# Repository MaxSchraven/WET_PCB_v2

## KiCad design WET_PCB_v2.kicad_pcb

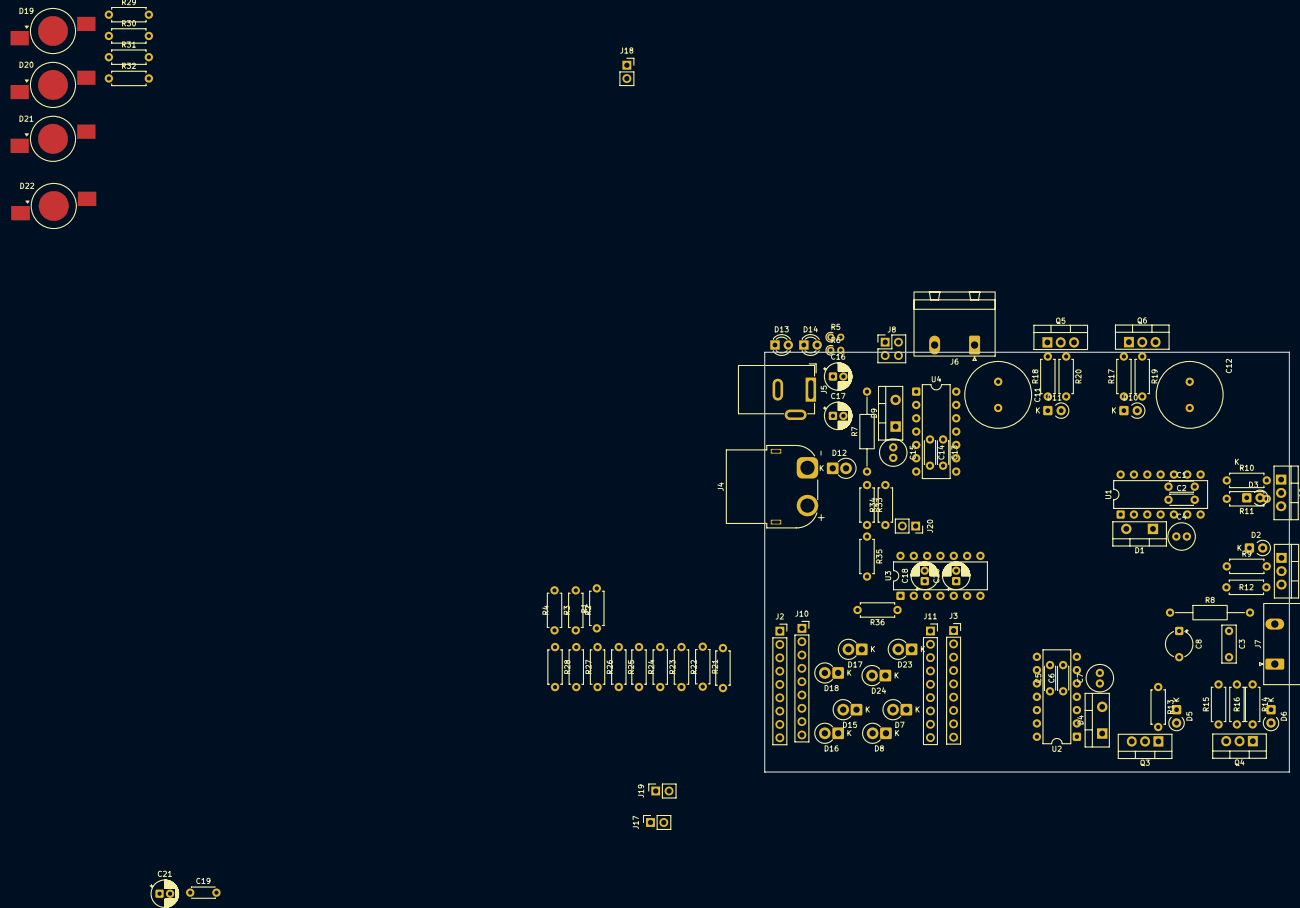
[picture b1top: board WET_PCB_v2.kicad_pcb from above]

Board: 2 copper layers, 100.0 x 80.0 mm, 102 parts (0 on the bottom side), 61 nets, no tracks yet.

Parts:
C1, C2, C5, C6, C13, C14, C19: C322C104K5R5TA; C_Disc_D4.3mm_W1.9mm_P5.00mm
C3: B32529C1104K000; C_Rect_L7.0mm_W2.5mm_P5.00mm
C4, C7, C15: MCGPR63V106M5X11; C_Radial_D5.0mm_H11.0mm_P2.00mm
C8: C; CP_Radial_Tantal_D5.0mm_P5.00mm
C11, C12: C_Polarized; C_Radial_D12.5mm_H20.0mm_P5.00mm
C16, C17, C18, C20, C21: C_Polarized; CP_Radial_D5.0mm_P2.00mm
D1, D4, D9: STPS8H100D; TO-220-2_Vertical
D2, D3, D5, D6, D10, D11: 1N4004; D_A-405_P2.54mm_Vertical_CathodeUp
D7, D8, D15, D16, D17, D18, D23, D24: 1N4004; D_DO-15_P2.54mm_Vertical_CathodeUp
D12: MBR1020VL; D_DO-15_P2.54mm_Vertical_CathodeUp
D13, D14: LED; LED_D3.0mm
D19, D20, D21, D22: LED; LED_1W_3W_R8
J2, J3, J10, J11: Conn_01x09_Pin; PinSocket_1x09_P2.54mm_Vertical
J4: XT60; AMASS_XT60PW-F_1x02_P7.20mm_Horizontal
J5: Barrel jack; BarrelJack_GCT_DCJ200-10-A_Horizontal
J6, J7: Pluggable Terminal Block; PhoenixContact_GMSTBA_2,5_2-G-7,62_1x02_P7.62mm_Horizontal
J8: Jumper; PinHeader_2x02_P2.54mm_Vertical
J17, J18, J19, J20: Capacitor connector; PinSocket_1x02_P2.54mm_Vertical
Q1, Q2, Q3, Q4: IRF530NPBF; TO-220-3_Vertical
Q5, Q6: Q_NMOS_GDS; TO-220-3_Vertical
R1, R2, R3, R4, R21, R22, R23, R24, R25, R26, R27, R28, R29, R30, R31, R32, R33, R34, R35, R36: R; R_Axial_DIN0207_L6.3mm_D2.5mm_P7.62mm_Horizontal
R5, R6: R; R_Axial_DIN0204_L3.6mm_D1.6mm_P1.90mm_Vertical
R7, R8: Shunt; R_Axial_DIN0207_L6.3mm_D2.5mm_P15.24mm_Horizontal
R9, R10, R11, R12, R13, R14, R15, R16, R17, R18, R19, R20: MF25_10K; R_Axial_DIN0207_L6.3mm_D2.5mm_P7.62mm_Horizontal
U1, U2, U4: IR2110; DIP-14_W7.62mm
U3: Opamp_Quad; DIP-14_W7.62mm

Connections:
+5V: C18.1, C19.1, C20.1, C21.1, D7.1 (K), D15.1 (K), D17.1 (K), D23.1 (K), J8.4, R6.1, U3.4 (V+)
+12V: C16.1, C17.1, D1.2 (A), D4.2 (A), J2.9, J5.1, J10.9, R5.1, U1.3 (VCC), U2.3 (VCC)
/ADC1_IN0: J3.5, J11.5
/ADC1_IN1: D15.2 (A), D16.1 (K), D17.2 (A), D18.1 (K), J3.6, J11.6, R22.2, R28.2, U3.8 (out3), U3.14 (out4)
/ADC1_IN4: D7.2 (A), D8.1 (K), J2.2, J10.2, J17.2, R4.2
/ADC1_IN5: D23.2 (A), D24.1 (K), J2.3, J10.3, J18.2, R36.2
/DCDC/DCDC_coil_circuit_side: C11.1, C14.1, C15.1 (+), J6.1, Q5.2 (D), Q6.2 (D), R19.1, U4.5 (VS)
/DCDC/DCDC_coil_input_side: J6.2, R7.2, R21.1
/DCDC/Gatedriver/Q1_gate: D11.2 (A), Q5.1 (G), R18.2, R20.2
/DCDC/Gatedriver/Q2_gate: D10.2 (A), Q6.1 (G), R17.2, R19.2
/DCDC/Gatedriver/VCC_Driver: D9.2 (A), U4.3 (VCC)
/DCDC/Gatedriver/VDD_Driver_DCDC: C13.2, U4.9 (VDD)
/DCDC/VoutDCDC: C12.1, Q1.2 (D), Q3.2 (D), Q6.3 (S)
/GPIO_A12: J2.7, J10.7
/GPIO_PC15: J3.4, J11.4
/SYS_NRST: J3.1, J11.1
/TIM1_CH4: J2.6, J10.6, R29.2, R30.2, R31.2, R32.2
/TIM3_CH1: J2.8, J10.8, U1.10 (HIN), U2.12 (LIN)
/TIM3_CH2: J2.4, J10.4, U1.12 (LIN), U2.10 (HIN)
/TIM14_CH1: J2.5, J10.5
/TIM17_CH1: J3.3, J11.3
/TIM17_CH1N: J3.2, J11.2
/USART2_RX: J3.8, J11.8
/USART2_TX: J3.7, J11.7
/currsense_inv/Shunt_from_source: R8.1, R26.1
/currsense_inv/Shunt_to_load: R8.2, R25.1
/inverter/VDD_Inverter: C1.2, C5.2, U1.9 (VDD), U2.9 (VDD)
/inverter/Vout_Inverter_+: C2.1, C3.1, C4.1 (+), C8.1, J7.2, Q1.3 (S), Q2.2 (D), R12.1, U1.5 (VS)
/inverter/Vout_Inverter_-: C3.2, C6.1, C7.1 (+), C8.2, J7.1, Q3.3 (S), Q4.2 (D), R15.1, U2.5 (VS)
GND: C1.1, C5.1, C11.2, C12.2, C13.1, C16.2, C17.2, C18.2, C19.2, C20.2, C21.2, D8.2 (A), D13.1 (K), D14.1 (K), D16.2 (A), D18.2 (A), D19.1 (K), D20.1 (K), D21.1 (K), D22.1 (K), D24.2 (A), J2.1, J3.9, J4.2, J5.2, J8.1, J8.2, J10.1, J11.9, J17.1, J18.1, J19.1, J20.1, Q2.3 (S), Q4.3 (S), Q5.3 (S), R2.2, R11.1, R16.1, R20.1, R24.1, R27.1, R34.2, U1.2 (COM), U1.11 (SD), U1.13 (VSS), U2.2 (COM), U2.11 (SD), U2.13 (VSS), U3.11 (V-), U4.2 (COM), U4.13 (VSS)
unnamed: C2.2, C4.2 (-), D1.1 (K), U1.6 (VB)
unnamed: C6.2, C7.2 (-), D4.1 (K), U2.6 (VB)
unnamed: C14.2, C15.2 (-), D9.1 (K), U4.6 (VB)
unnamed: D2.2 (A), Q1.1 (G), R9.2, R12.2
unnamed: D2.1 (K), R9.1, U1.7 (HO)
unnamed: D3.2 (A), Q2.1 (G), R10.2, R11.2
unnamed: D3.1 (K), R10.1, U1.1 (LO)
unnamed: D5.2 (A), Q3.1 (G), R13.2, R15.2
unnamed: D5.1 (K), R13.1, U2.7 (HO)
unnamed: D6.2 (A), Q4.1 (G), R14.2, R16.2
unnamed: D6.1 (K), R14.1, U2.1 (LO)
unnamed: D10.1 (K), R17.1, U4.7 (HO)
unnamed: D11.1 (K), R18.1, U4.1 (LO)
unnamed: D12.2 (A), J4.1
unnamed: D13.2 (A), R5.2
unnamed: D14.2 (A), R6.2
unnamed: D19.2 (A), R29.1
unnamed: D20.2 (A), R30.1
unnamed: D21.2 (A), R31.1
unnamed: D22.2 (A), R32.1
unnamed: J19.2, R1.2, R2.1, R3.1
unnamed: J20.2, R33.2, R34.1, R35.1
unnamed: R35.2, U3.3 (+)
unnamed: R36.1, U3.1, U3.2 (-)
unnamed: R3.2, U3.5 (in2+)
unnamed: R4.1, U3.6 (in2-), U3.7 (out2)
unnamed: R23.2, R24.2, U3.10 (in3+)
unnamed: R21.2, R22.1, U3.9 (in3-)
unnamed: R26.2, R27.2, U3.12 (in4+)
unnamed: R25.2, R28.1, U3.13 (in4-)
VPP: D12.1 (K), R7.1, R23.1, R33.1

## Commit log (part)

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2026-05-10 Autosave
2026-05-10 SCH Save: 1 files changed currsense_DCDC.kicad_sch 0/0/1
2026-05-10 SCH Save: 1 files changed DCDC.kicad_sch 0/0/1
2026-05-10 SCH Save: 2 files changed 12v5V.kicad_sch 0/0/2 GateDriver.kicad_sch 0/0/8
2026-05-10 SCH Save: 1 files changed decoration.kicad_sch 0/0/1
2026-05-10 SCH Save: 1 files changed 12v5V.kicad_sch 0/0/3
2026-05-10 SCH Save: 1 files changed GateDriver.kicad_sch 0/0/8
2026-05-10 SCH Save: 2 files changed WET_PCB_v2.kicad_sch 0/0/4 ~WET_PCB_v2.kicad_pcb.lck 1/0/0
2026-05-10 SCH Save: 1 files changed 12v5V.kicad_sch 0/0/1
2026-05-10 SCH Save: 1 files changed voltsense_DCDC.kicad_sch 0/0/4
2026-05-10 SCH Save: 2 files changed currsense_DCDC.kicad_sch 1/0/2 voltsense_DCDC.kicad_sch 0/0/4
2026-05-10 SCH Save: 1 files changed currsense_DCDC.kicad_sch 0/1/5
2026-05-10 SCH Save: 1 files changed voltsense_DCDC.kicad_sch 0/0/2
2026-05-10 SCH Save: 1 files changed WET_PCB_v2.kicad_sch 0/0/64
2026-05-10 SCH Save: 1 files changed WET_PCB_v2.kicad_sch 0/0/2
2026-05-10 SCH Save: 1 files changed WET_PCB_v2.kicad_sch 10/0/0
2026-05-10 SCH Save: 1 files changed WET_PCB_v2.kicad_sch 0/0/1
2026-05-10 most footprints added (some random)
2026-05-10 SCH Save: 1 files changed DCDC.kicad_sch 0/0/3
2026-05-10 SCH Save: 7 files changed currsense_inv.kicad_sch 2397/0/0 MCU.kicad_sch 0/0/1 WET_PCB_v2.kicad_pcb 0/6293/0 WET_PCB_v2.kicad_prl 138/0/0 WET_PCB_v2.kicad_pro 741/0/0 ~WET_PCB_v2.kicad_pcb.lck 1/0/0 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
2026-05-10 SCH Save: 1 files changed DCDC.kicad_sch 0/10/0
2026-05-10 SCH Save: 1 files changed DCDC.kicad_sch 10/0/1
2026-05-10 PCB Save: 1 files changed WET_PCB_v2.kicad_pcb 32412/0/0
2026-05-10 SCH Save: 4 files changed DCDC.kicad_sch 0/0/2 WET_PCB_v2.kicad_pcb 0/996/3226 WET_PCB_v2.kicad_prl 0/0/1 WET_PCB_v2.kicad_sch 0/0/2
2026-05-10 PCB Save: 1 files changed WET_PCB_v2.kicad_sch 0/0/1
2026-05-10 SCH Save: 4 files changed currsense_DCDC.kicad_sch 0/0/2 voltsense_DCDC.kicad_sch 0/0/2 voltsense_inverter.kicad_sch 0/0/2 WET_PCB_v2.kicad_pcb 0/0/13
2026-05-10 SCH Save: 1 files changed voltsense_inverter.kicad_sch 0/0/2
2026-05-10 SCH Save: 1 files changed currsense_DCDC.kicad_sch 0/0/3
2026-05-10 PCB Save: 1 files changed WET_PCB_v2.kicad_pcb 0/0/1
2026-05-10 SCH Save: 2 files changed WET_PCB_v2.kicad_pcb 156/0/492 WET_PCB_v2.kicad_sch 0/1/79
2026-05-10 PCB Save: 1 files changed WET_PCB_v2.kicad_sch 0/0/2
2026-05-10 PCB Save: 2 files changed WET_PCB_v2.kicad_prl 0/0/1 WET_PCB_v2.kicad_sch 0/0/2
2026-05-10 SCH Save: 2 files changed GateDriver.kicad_sch 0/0/2 WET_PCB_v2.kicad_pcb 180/0/247
2026-05-10 SCH Save: 1 files changed GateDriver.kicad_sch 10/0/2
2026-05-10 SCH Save: 1 files changed WET_PCB_v2.kicad_pcb 180/0/566
2026-05-10 SCH Save: 1 files changed inverter.kicad_sch 0/0/4
2026-05-10 PCB Save: 1 files changed WET_PCB_v2.kicad_pcb 0/0/2
2026-05-10 SCH Save: 2 files changed WET_PCB_v2.kicad_pcb 0/0/124 WET_PCB_v2.kicad_sch 0/1/6
2026-05-10 made a rough layout now i go eep
2026-05-10 PCB Save: 6 files changed currsense_inv.kicad_sch 2397/0/0 MCU.kicad_sch 0/0/1 WET_PCB_v2.kicad_prl 138/0/0 WET_PCB_v2.kicad_pro 741/0/0 ~WET_PCB_v2.kicad_pcb.lck 1/0/0 ~WET_PCB_v2.kicad_sch.lck 1/0/0
2026-05-10 update before closing software
